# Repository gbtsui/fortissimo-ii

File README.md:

# fortissimo ii

Hello world!

This is my 2nd attempt at building a keyboard.

I really enjoyed hackpad v2 (even though mine ended up broken...) and I wanted an extra little challenge to build something bigger and get better at soldering. So I designed this ortholinear split keyboard that's ideally meant to be perfect for me; ergonomic design, looks cool, a lot of functionality, and on-the-fly custom language switching (eventually - firmware hasn't caught up to that yet!). Since I'm planning on phasing out my laptop when the school year starts to avoid distractions a bit better, I'm going to hopefully replace it with an iPad so I can take notes more effectively. But because I don't have enough money for an iPad keyboard (I'm not shelling out another $160 after buying a $400 device plus a $100 pencil), and I wanted to challenge myself to design something that might be able to replace it, I designed this instead.

Maybe it's not the prettiest case (blame my awful CAD skills, also it's actually asymmetrical in size) and doesn't have the most beautiful design (I'm no electrical engineer), but hopefully it'll work. 

Also, yes, this keyboard is piano themed. I like pianos. I am not good at playing piano. But I thought it was a cool concept.

## Bill of Materials

| Item | Cost (each) | Quantity | Subtotal | Shipping |
|---|---|---|---|---|
|[kailh choc v1 brown](https://chosfox.com/collections/kailh-low-profile-switch-pg1350/products/kailh-chocs?variant=42514647646402) | $0.48 (10 pack) | 70 | $33.60 | $8.45 |
|[trrs jack](https://www.aliexpress.com/item/32368285821.html) | $0.069 (20 pack) | 2 | $1.38 | $4.35 |
|[128x64 SSD1306 OLED](https://www.aliexpress.com/item/1005006700828250.html) | $1.15 | 2 | $2.30 | Free Shipping |
| digikey |---|---|---|$8.00|
|[1N4148FS-ND matrix diodes](https://www.digikey.ca/en/products/detail/onsemi/1N4148/458603) | $0.0486 (100 pack) | 70 | $4.86 | - |
|[PESD5V0S1UL ESD protection diode](https://www.digikey.ca/en/products/detail/nexperia-usa-inc/PESD5V0S1BA-QF/18108466) | $0.311 (10 pack) | 6 | $3.11 | - |
|[6mm tactile switch](https://www.digikey.ca/en/products/detail/same-sky-formerly-cui-devices-/TS02-66-50-BK-100-LCR-D/15634294) | $0.15 | 1 | $0.15 | - |
|[raspberry pi pico](https://www.digikey.ca/en/products/detail/raspberry-pi/SC0915/13684020) | $5.75 | 1 | $5.75 | - |
|[4.7k pull up resistor](https://www.digikey.ca/en/products/detail/yageo/RC0603FR-074K7L/727212) | $0.014 (10 pack) | 4 | $0.14 | - |
|[header pin](https://www.digikey.ca/en/products/detail/w-rth-elektronik/61301611121/4846854) | $1.25 | 1 | $1.25 | - | 
|[M3 10mm heatset insert](https://www.digikey.ca/en/products/detail/adafruit-industries-llc/4255/10244656) | $0.1826 (50 pack) | 10 | $9.13 | - |
|[M3 10mm screw](https://www.digikey.ca/en/products/detail/apm-hexseal/RM3X10MM-2701/3712296) | $0.753 (10 pack) | 10 | $7.53 | - |
|PCB| $6.69 (5 pack, including shipping) |  1 | $17.60 | $12.67 + $3.17 | 

Total: $123.44

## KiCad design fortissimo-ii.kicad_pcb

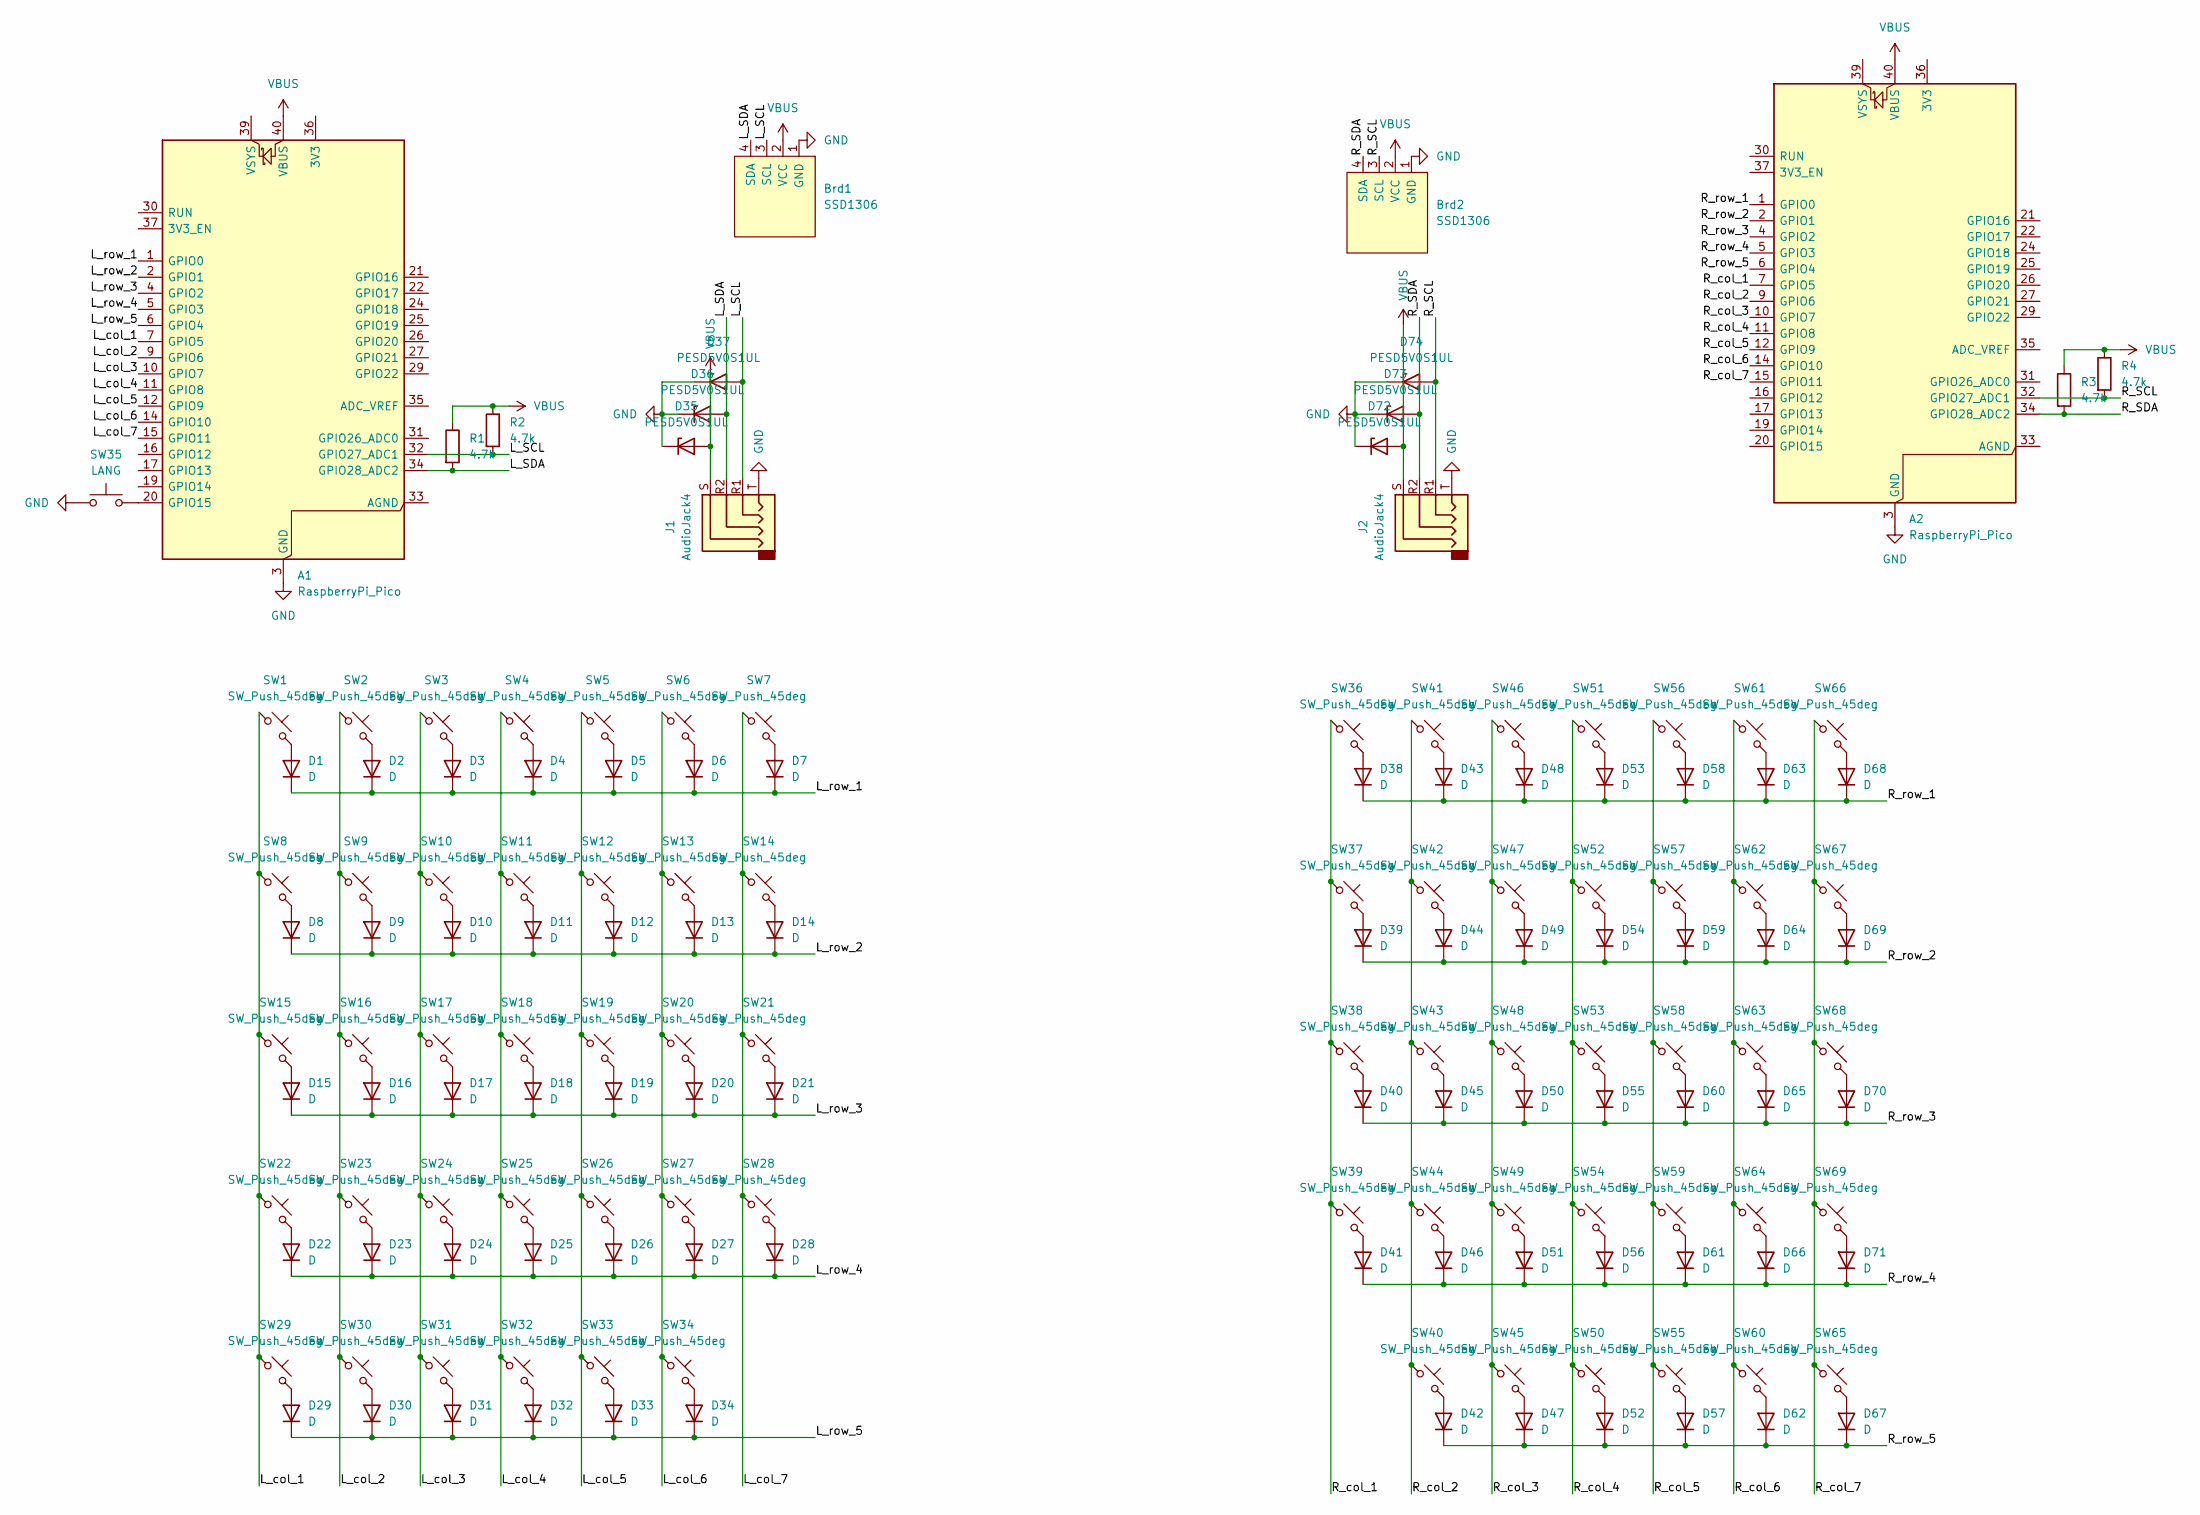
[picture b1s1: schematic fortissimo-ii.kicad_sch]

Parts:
A1, A2: RaspberryPi_Pico; RaspberryPi_Pico_Common_Unspecified
Brd1, Brd2: SSD1306; 128x64OLED
D1, D2, D3, D4, D5, D6, D7, D8, D9, D10, D11, D12, D13, D14, D15, D16, D17, D18, D19, D20, D21, D22, D23, D24, D25, D26, D27, D28, D29, D30, D31, D32, D33, D34, D38, D39, D40, D41, D42, D43, D44, D45, D46, D47, D48, D49, D50, D51, D52, D53, D54, D55, D56, D57, D58, D59, D60, D61, D62, D63, D64, D65, D66, D67, D68, D69, D70, D71: D; D_DO-35_SOD27_P7.62mm_Horizontal
D35, D36, D37, D72, D73, D74: PESD5V0S1UL; D_SOD-882
J1, J2: AudioJack4; TRRS-PJ-320A
R1, R2, R3, R4: 4.7k; R_0603_1608Metric
SW1, SW2, SW3, SW4, SW5, SW6, SW7, SW8, SW9, SW10, SW11, SW12, SW13, SW14, SW15, SW16, SW17, SW18, SW19, SW20, SW21, SW22, SW23, SW24, SW25, SW26, SW27, SW28, SW29, SW30, SW31, SW32, SW33, SW36, SW37, SW38, SW39, SW41, SW42, SW43, SW44, SW45, SW46, SW47, SW48, SW49, SW50, SW51, SW52, SW53, SW54, SW55, SW56, SW57, SW58, SW59, SW60, SW61, SW62, SW63, SW64, SW65, SW66, SW67, SW68, SW69: SW_Push_45deg; Low-Profile-Choc-MX
SW34, SW40: SW_Push_45deg; MX-Alps-Choc-2U-StabFlip
SW35: LANG; SW_PUSH_6mm

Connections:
/L_SCL: A1.32 (GPIO27_ADC1), Brd1.3 (SCL), D37.2 (A), J1.R1, R2.2
/L_SDA: A1.34 (GPIO28_ADC2), Brd1.4 (SDA), D36.2 (A), J1.R2, R1.2
/L_col_1: A1.7 (GPIO5), SW1.1, SW8.1, SW15.1, SW22.1, SW29.1
/L_col_2: A1.9 (GPIO6), SW2.1, SW9.1, SW16.1, SW23.1, SW30.1
/L_col_3: A1.10 (GPIO7), SW3.1, SW10.1, SW17.1, SW24.1, SW31.1
/L_col_4: A1.11 (GPIO8), SW4.1, SW11.1, SW18.1, SW25.1, SW32.1
/L_col_5: A1.12 (GPIO9), SW5.1, SW12.1, SW19.1, SW26.1, SW33.1
/L_col_6: A1.14 (GPIO10), SW6.1, SW13.1, SW20.1, SW27.1, SW34.1
/L_col_7: A1.15 (GPIO11), SW7.1, SW14.1, SW21.1, SW28.1
/L_row_1: A1.1 (GPIO0), D1.1 (K), D2.1 (K), D3.1 (K), D4.1 (K), D5.1 (K), D6.1 (K), D7.1 (K)
/L_row_2: A1.2 (GPIO1), D8.1 (K), D9.1 (K), D10.1 (K), D11.1 (K), D12.1 (K), D13.1 (K), D14.1 (K)
/L_row_3: A1.4 (GPIO2), D15.1 (K), D16.1 (K), D17.1 (K), D18.1 (K), D19.1 (K), D20.1 (K), D21.1 (K)
/L_row_4: A1.5 (GPIO3), D22.1 (K), D23.1 (K), D24.1 (K), D25.1 (K), D26.1 (K), D27.1 (K), D28.1 (K)
/L_row_5: A1.6 (GPIO4), D29.1 (K), D30.1 (K), D31.1 (K), D32.1 (K), D33.1 (K), D34.1 (K)
/R_SCL: A2.32 (GPIO27_ADC1), Brd2.3 (SCL), D74.2 (A), J2.R1, R4.2
/R_SDA: A2.34 (GPIO28_ADC2), Brd2.4 (SDA), D73.2 (A), J2.R2, R3.2
/R_col_1: A2.7 (GPIO5), SW36.1, SW37.1, SW38.1, SW39.1
/R_col_2: A2.9 (GPIO6), SW40.1, SW41.1, SW42.1, SW43.1, SW44.1
/R_col_3: A2.10 (GPIO7), SW45.1, SW46.1, SW47.1, SW48.1, SW49.1
/R_col_4: A2.11 (GPIO8), SW50.1, SW51.1, SW52.1, SW53.1, SW54.1
/R_col_5: A2.12 (GPIO9), SW55.1, SW56.1, SW57.1, SW58.1, SW59.1
/R_col_6: A2.14 (GPIO10), SW60.1, SW61.1, SW62.1, SW63.1, SW64.1
/R_col_7: A2.15 (GPIO11), SW65.1, SW66.1, SW67.1, SW68.1, SW69.1
/R_row_1: A2.1 (GPIO0), D38.1 (K), D43.1 (K), D48.1 (K), D53.1 (K), D58.1 (K), D63.1 (K), D68.1 (K)
/R_row_2: A2.2 (GPIO1), D39.1 (K), D44.1 (K), D49.1 (K), D54.1 (K), D59.1 (K), D64.1 (K), D69.1 (K)
/R_row_3: A2.4 (GPIO2), D40.1 (K), D45.1 (K), D50.1 (K), D55.1 (K), D60.1 (K), D65.1 (K), D70.1 (K)
/R_row_4: A2.5 (GPIO3), D41.1 (K), D46.1 (K), D51.1 (K), D56.1 (K), D61.1 (K), D66.1 (K), D71.1 (K)
/R_row_5: A2.6 (GPIO4), D42.1 (K), D47.1 (K), D52.1 (K), D57.1 (K), D62.1 (K), D67.1 (K)
GND: A1.3 (GND), A1.8 (GND), A1.13 (GND), A1.18 (GND), A1.23 (GND), A1.28 (GND), A1.38 (GND), A2.3 (GND), A2.8 (GND), A2.13 (GND), A2.18 (GND), A2.23 (GND), A2.28 (GND), A2.38 (GND), Brd1.1 (GND), Brd2.1 (GND), D35.1 (K), D36.1 (K), D37.1 (K), D72.1 (K), D73.1 (K), D74.1 (K), J1.T, J2.T, SW35.2
unnamed: A1.20 (GPIO15), SW35.1
unnamed: D1.2 (A), SW1.2
unnamed: D2.2 (A), SW2.2
unnamed: D3.2 (A), SW3.2
unnamed: D4.2 (A), SW4.2
unnamed: D5.2 (A), SW5.2
unnamed: D6.2 (A), SW6.2
unnamed: D7.2 (A), SW7.2
unnamed: D8.2 (A), SW8.2
unnamed: D9.2 (A), SW9.2
unnamed: D10.2 (A), SW10.2
unnamed: D11.2 (A), SW11.2
unnamed: D12.2 (A), SW12.2
unnamed: D13.2 (A), SW13.2
unnamed: D14.2 (A), SW14.2
unnamed: D15.2 (A), SW15.2
unnamed: D16.2 (A), SW16.2
unnamed: D17.2 (A), SW17.2
unnamed: D18.2 (A), SW18.2
unnamed: D19.2 (A), SW19.2
unnamed: D20.2 (A), SW20.2
unnamed: D21.2 (A), SW21.2
unnamed: D22.2 (A), SW22.2
unnamed: D23.2 (A), SW23.2
unnamed: D24.2 (A), SW24.2
unnamed: D25.2 (A), SW25.2
unnamed: D26.2 (A), SW26.2
unnamed: D27.2 (A), SW27.2
unnamed: D28.2 (A), SW28.2
unnamed: D29.2 (A), SW29.2
unnamed: D30.2 (A), SW30.2
unnamed: D31.2 (A), SW31.2
unnamed: D32.2 (A), SW32.2
unnamed: D33.2 (A), SW33.2
unnamed: D34.2 (A), SW34.2
unnamed: D38.2 (A), SW36.2
unnamed: D39.2 (A), SW37.2
unnamed: D40.2 (A), SW38.2
unnamed: D41.2 (A), SW39.2
unnamed: D42.2 (A), SW40.2
unnamed: D43.2 (A), SW41.2
unnamed: D44.2 (A), SW42.2
unnamed: D45.2 (A), SW43.2
unnamed: D46.2 (A), SW44.2
unnamed: D47.2 (A), SW45.2
unnamed: D48.2 (A), SW46.2
unnamed: D49.2 (A), SW47.2
unnamed: D50.2 (A), SW48.2
unnamed: D51.2 (A), SW49.2
unnamed: D52.2 (A), SW50.2
unnamed: D53.2 (A), SW51.2
unnamed: D54.2 (A), SW52.2
unnamed: D55.2 (A), SW53.2
unnamed: D56.2 (A), SW54.2
unnamed: D57.2 (A), SW55.2
unnamed: D58.2 (A), SW56.2
unnamed: D59.2 (A), SW57.2
unnamed: D60.2 (A), SW58.2
unnamed: D61.2 (A), SW59.2
unnamed: D62.2 (A), SW60.2
unnamed: D63.2 (A), SW61.2
unnamed: D64.2 (A), SW62.2
unnamed: D65.2 (A), SW63.2
unnamed: D66.2 (A), SW64.2
unnamed: D67.2 (A), SW65.2
unnamed: D68.2 (A), SW66.2
unnamed: D69.2 (A), SW67.2
unnamed: D70.2 (A), SW68.2
unnamed: D71.2 (A), SW69.2
VBUS: A1.40 (VBUS), A2.40 (VBUS), Brd1.2 (VCC), Brd2.2 (VCC), D35.2 (A), D72.2 (A), J1.S, J2.S, R1.1, R2.1, R3.1, R4.1

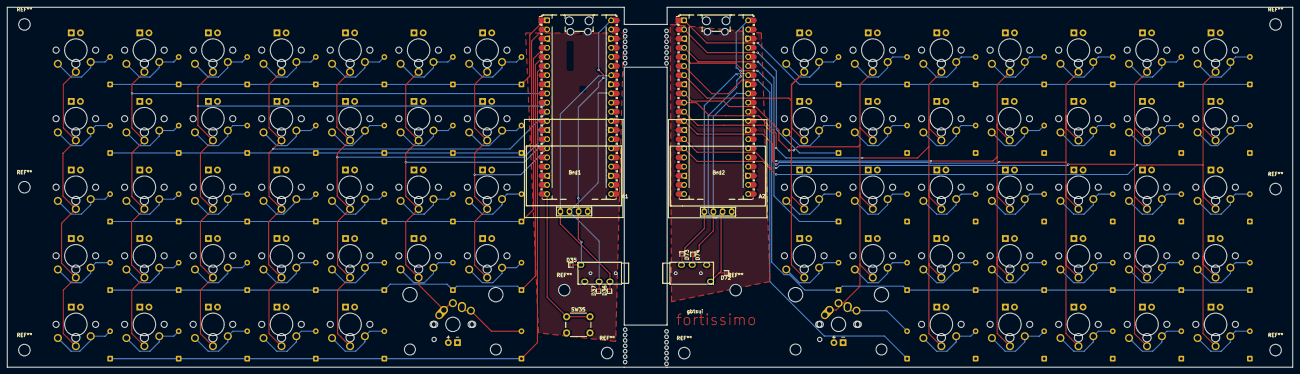
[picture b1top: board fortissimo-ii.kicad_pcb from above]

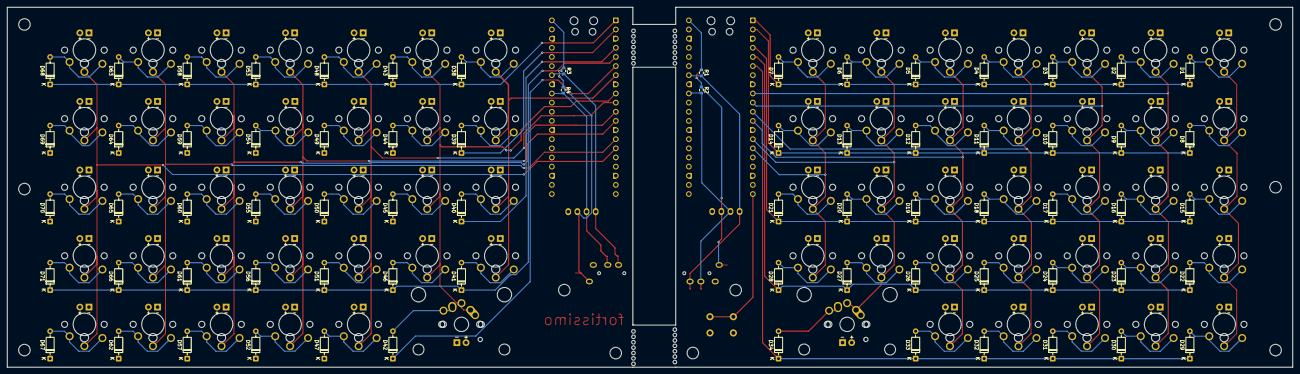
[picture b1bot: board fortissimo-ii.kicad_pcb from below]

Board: 2 copper layers, 357.2 x 100.0 mm, 153 parts (72 on the bottom side), 99 nets.

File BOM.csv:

"Id";"Designator";"Footprint";"Quantity";"Designation";"Supplier and ref";
1;"SW9,SW43,SW48,SW21,SW26,SW29,SW52,SW61,SW64,SW56,SW62,SW2,SW54,SW31,SW65,SW25,SW4,SW14,SW8,SW6,SW5,SW67,SW46,SW66,SW18,SW20,SW37,SW1,SW24,SW57,SW27,SW68,SW36,SW32,SW3,SW58,SW33,SW63,SW53,SW22,SW60,SW44,SW11,SW39,SW7,SW23,SW13,SW55,SW10,SW41,SW51,SW12,SW49,SW47,SW17,SW28,SW59,SW19,SW16,SW42,SW50,SW38,SW15,SW30,SW45,SW69";"Low-Profile-Choc-MX";66;"SW_Push_45deg";"Switches";"https://chosfox.com/collections/kailh-low-profile-switch-pg1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";
2;"J2,J1";"TRRS-PJ-320A";2;"AudioJack4";"TRRS";"https://keeb.io/products/trrs-jack-3-5mm";
3;"D58,D70,D43,D51,D46,D54,D49,D60,D57,D64,D63,D44,D71,D38,D42,D52,D55,D67,D40,D62,D47,D45,D59,D68,D53,D48,D61,D65,D56,D69,D41,D39,D50,D66,D10,D23,D21,D27,D11,D12,D8,D15,D13,D25,D14,D26,D19,D16,D28,D31,D3,D18,D1,D29,D5,D34,D17,D32,D22,D9,D33,D30,D2,D24,D4,D7,D6,D20";"D_DO-35_SOD27_P7.62mm_Horizontal";68;"D";"Matrix Diodes";"https://www.digikey.ca/en/products/detail/onsemi/1N4148/458603";
4;"D72,D37,D73,D36,D35,D74";"D_SOD-882";6;"PESD5V0S1UL";"ESD Protection Diode";"https://www.digikey.ca/en/products/detail/nexperia-usa-inc/P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";
5;"SW34,SW40";"MX-Alps-Choc-2U-StabFlip";2;"SW_Push_45deg";"Switches";"https://chosfox.com/collections/kailh-low-profile-switch-pg1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";
6;"Brd2,Brd1";"128x64OLED";2;"SSD1306";"OLED Display";"https://www.aliexpress.com/item/1005006700828250.html";
7;"SW35";"SW_PUSH_6mm";1;"LANG";"Language Switch Button";"https://www.digikey.ca/en/products/detail/same-sky-formerly-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";
8;"A1,A2";"RaspberryPi_Pico_Common_Unspecified";2;"RaspberryPi_Pico";"MCU";"https://www.digikey.ca/en/products/detail/raspberry-pi/SC091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";
9;"R4,R1,R3,R2";"R_0603_1608Metric";4;"4.7k";"I2C Pull-Up Resistors";"https://www.digikey.ca/en/products/detail/yageo/RC0603FR-074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";
10; "";"";1;";"Header Pins";"https://www.digikey.ca/en/products/detail/w-rth-elektronik/6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";
11; "";"";10;"";"Heatset Inserts for Screws";"https://www.digikey.ca/en/products/detail/adafruit-industrie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";
12; "";"";10;"";"Screws";"https://www.canadarobotix.com/products/831?variant=144235655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"

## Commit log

2025-06-04 init
2025-06-04 added journal
2025-06-04 first log
2025-06-13 created schematic v1
2025-06-17 wired up neopixels
2025-06-17 finished left side!
2025-07-30 changes from jul 29
2025-07-30 i think something got broken
2025-08-01 basically the entire thing
2025-08-01 README
2025-08-05 fix BOM
2025-08-06 new image
2025-08-06 journal update
2025-08-16 final polish
2025-08-16 updated readme slightly
